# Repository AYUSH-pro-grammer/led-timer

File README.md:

# Blinky Board 

LED chase ("blinky") circuit created for beginners in **Stasis**.

## Components

**NE555 timer** as a pulse generator
**CD4017 decade counter** to control outputs
Several LEDs as indicators

Pulses generated by the 555 timer trigger the 4017, which switches LEDs to form a running light.

## Advantages

Speed control using potentiometer
Easy and newbie-friendly design
Use of popular parts
Perfect for digital & analog electronics basics education

## Folder Structure

```
.
├── bom.csv              # Bill of materials
├── grb 2.zip            # Gerber files for PCB manufacturing
├── image/
│   ├── schematic.png    # Circuit diagram
│   ├── pcb.png          # PCB layout
│   └── 3d.png           # 3D view
├── kicad/
│   ├── StarLight.kicad_sch
│   ├── StarLight.kicad_pcb
│   └── StarLight.kicad_pro
└── README.md
```

## How it works

1. The **NE555** chip functions in astable configuration to produce clock pulses.
2. Clock pulses are fed into the **CD4017** counter.
3. The counter shifts from one output to another.
4. Outputs activate LEDs to produce the chaser effect.

## Quick start guide

1. Load the project in **KiCad**
2. Examine the circuit and board diagrams
3. Generate Gerbers (or download ZIP file)
4. Order PCB or assemble on protoboard
5. Install components from `bom.csv`

## Preview

* Schematic: `image/schematic.png`
  
* PCB: `image/pcb.png`
  
* 3D View: `image/3d.png`

Developed as a basic hardware project

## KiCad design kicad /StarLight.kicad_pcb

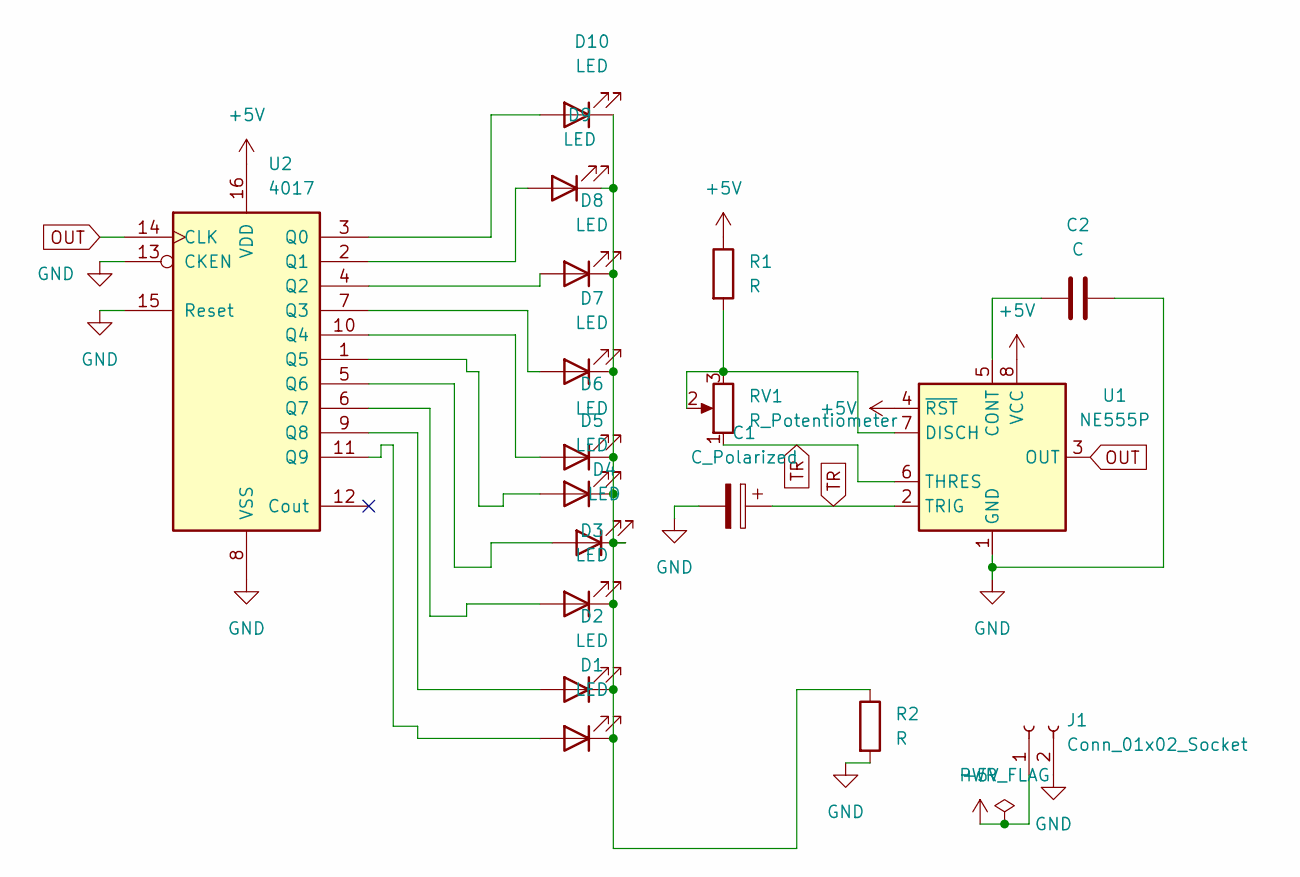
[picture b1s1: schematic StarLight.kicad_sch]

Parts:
C1: C_Polarized; CP_Radial_D5.0mm_P2.00mm
C2: C; C_Disc_D7.5mm_W2.5mm_P5.00mm
D1, D2, D3, D4, D5, D6, D7, D8, D9, D10: LED; LED_D3.0mm
J1: Conn_01x02_Socket; PinHeader_1x02_P2.54mm_Vertical
R1, R2: R; R_Axial_DIN0207_L6.3mm_D2.5mm_P7.62mm_Horizontal
RV1: R_Potentiometer; Potentiometer_Vishay_T93YA_Vertical
U1: NE555P; DIP-8_W7.62mm
U2: 4017; DIP-16_W7.62mm

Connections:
+5V: J1.1, R1.1, U1.4 (~RST), U1.8 (VCC), U2.16 (VDD)
GND: C1.2, C2.2, J1.2, R2.2, U1.1 (GND), U2.8 (VSS), U2.13 (CKEN), U2.15 (Reset)
unnamed: D1.2 (A), U2.11 (Q9)
unnamed: D1.1 (K), D2.1 (K), D3.1 (K), D4.1 (K), D5.1 (K), D6.1 (K), D7.1 (K), D8.1 (K), D9.1 (K), D10.1 (K), R2.1
unnamed: D2.2 (A), U2.9 (Q8)
unnamed: D3.2 (A), U2.6 (Q7)
unnamed: D4.2 (A), U2.5 (Q6)
unnamed: D5.2 (A), U2.1 (Q5)
unnamed: D6.2 (A), U2.10 (Q4)
unnamed: D7.2 (A), U2.7 (Q3)
unnamed: D8.2 (A), U2.4 (Q2)
unnamed: D9.2 (A), U2.2 (Q1)
unnamed: D10.2 (A), U2.3 (Q0)
unnamed: C2.1, U1.5 (CONT)
unnamed: R1.2, RV1.2, RV1.3, U1.7 (DISCH)
OUT: U1.3 (OUT), U2.14 (CLK)
TR: C1.1, RV1.1, U1.2 (TRIG), U1.6 (THRES)

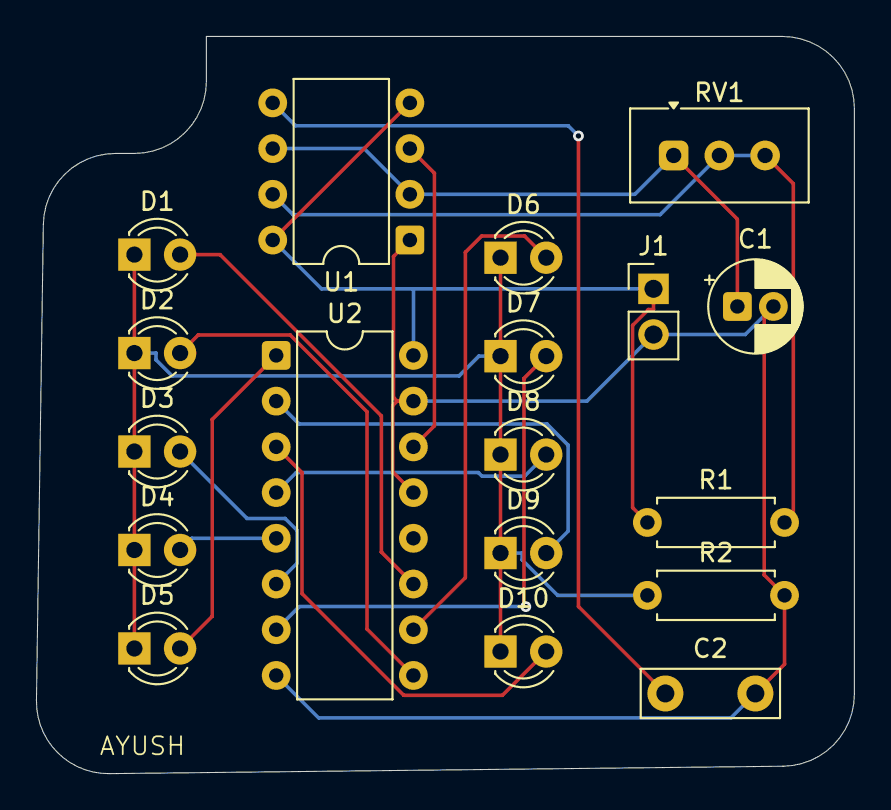
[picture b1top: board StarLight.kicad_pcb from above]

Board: 2 copper layers, 45.4 x 41.0 mm, 18 parts (0 on the bottom side), 17 nets.
